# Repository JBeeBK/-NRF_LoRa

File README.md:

# NRF_LoRa

PCB design for a Nordic nRF52840 (QFN48) with SX1262 LoRa module.  
Designed as a low-power mesh node for experimentation and LoRaWan or Meshtastic development.

### Features
- nRF52840 SoC (BLE, Cortex-M4F)
- SX1262 LoRa (868 MHz) with SMA antenna
- USB-C input with TPS2116 power multiplexer
- MCP73831 LiPo charger and MAX17048 fuel gauge
- 2 x I²C headers for OLED and maybe card keyboard
- FT231XS USB-UART bridge for programming
- Compact 4-layer PCB (60 x 45 mm)
- Additional Header for 2GPIO

### Repository Structure
- `Hardware/` – KiCad source files (schematic, PCB, symbols, footprints)
- `Documents/` – Excel for pinout and pins used, net labels, etc.
- `Output_Pcb/` – Gerbers, fabrication layer PDFs
- `Output_Assembly/` – BOM, pick-and-place, schematic PDFs
- `Firmware/` – C++ file

This repo documents the hardware design; firmware will be added once the board is fabricated.

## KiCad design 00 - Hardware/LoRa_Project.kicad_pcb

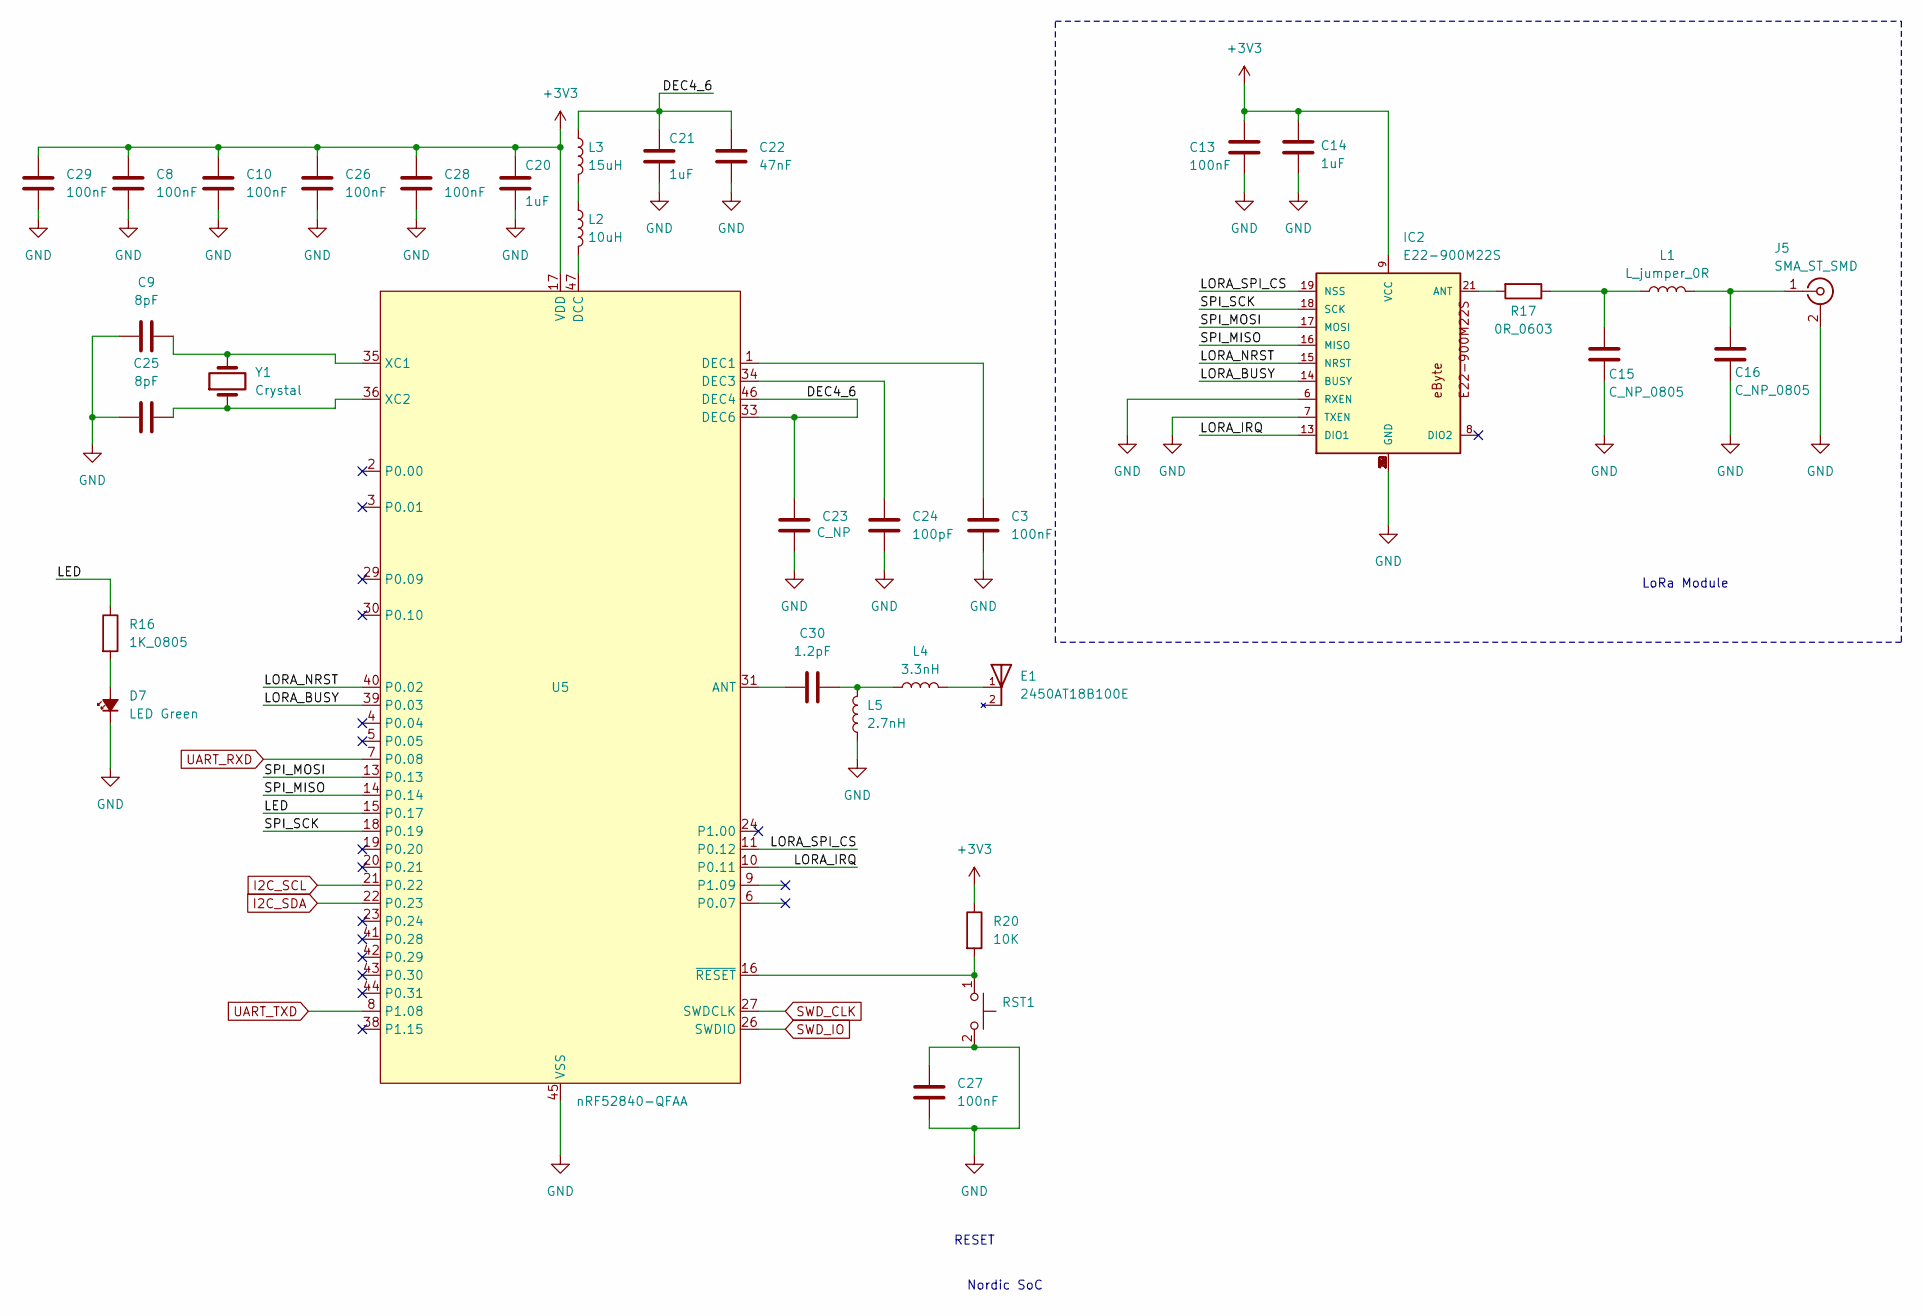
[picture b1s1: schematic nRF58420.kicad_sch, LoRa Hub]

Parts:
C3, C13, C27: 100nF; C_0603_1608Metric; MPN1 06033D104KAT2A
C8, C10, C26, C28, C29: 100nF; C_0402_1005Metric; MPN1 0402YC104KAT2A
C9, C25: 8pF; C_0603_1608Metric; MPN1 06033A8R0DAT2A
C14: 1uF; C_0805_2012Metric; MPN1 08053C105KAT2A
C15, C16: C_NP_0805; C_0805_2012Metric; MPN1 ---
C20, C21: 1uF; C_0603_1608Metric; MPN1 C0603C105K3RACTU
C22: 47nF; C_0603_1608Metric; MPN1 C0603X473J3RAC3316
C23: C_NP; C_0603_1608Metric; MPN1 ---
C24: 100pF; C_0603_1608Metric; MPN1 06033C101JAT4A
C30: 1.2pF; C_0402_1005Metric; MPN1 500R07S1R2BV4T
D7: LED Green; LED_0805; MPN1 APTD2012LCGCK
E1: 2450AT18B100E; XDCR_2450AT18B100E; MPN1 2450AT18B100E
IC2: E22-900M22S; MPN1 E22-900M22S
J5: SMA_ST_SMD; MPN1 CONSMA001-SMD-G
L1: L_jumper_0R; L_0805_2012Metric; MPN1 CRCW08050000Z0EA
L2: 10uH; L_0603_1608Metric; MPN1 LQW18AS10NG0ZD
L3: 15uH; L_0603_1608Metric; MPN1 LQW18AS10NG0ZD
L4: 3.3nH; L_0402_1005Metric; MPN1 L-07C3N3SV6T
L5: 2.7nH; L_0402_1005Metric; MPN1 L-07C2N7SV6T
R16: 1K_0805; R_0805_2012Metric; MPN1 CRCW08051K00FKEA
R17: 0R_0603; R_0603_1608Metric; MPN1 CRCW06030000Z0EAC
R20: 10K; R_0805_2012Metric; MPN1 CRCW080510K0FKEA
RST1: SW_Push_1P1T_NO_CK_KMR2; MPN1 KMR211NGLFS
U5: nRF52840-QFAA; QFN-48-1EP_6x6mm_P0.4mm_EP4.6x4.6mm_ThermalVias; MPN1 nRF52840-QFN
Y1: Crystal; Crystal_SMD_2016-4Pin_2.0x1.6mm; MPN1 XRCGB32M000F1SBJR0

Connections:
/nRF52840 and LoRa/DEC4_6: C21.1, C22.1, C23.1, L3.1, U5.33 (DEC6), U5.46 (DEC4)
/nRF52840 and LoRa/LED: R16.1, U5.15 (P0.17)
/nRF52840 and LoRa/LORA_BUSY: IC2.14 (BUSY), U5.39 (P0.03)
/nRF52840 and LoRa/LORA_IRQ: IC2.13 (DIO1), U5.10 (P0.11)
/nRF52840 and LoRa/LORA_NRST: IC2.15 (NRST), U5.40 (P0.02)
/nRF52840 and LoRa/LORA_SPI_CS: IC2.19 (NSS), U5.11 (P0.12)
/nRF52840 and LoRa/SPI_MISO: IC2.16 (MISO), U5.14 (P0.14)
/nRF52840 and LoRa/SPI_MOSI: IC2.17 (MOSI), U5.13 (P0.13)
/nRF52840 and LoRa/SPI_SCK: IC2.18 (SCK), U5.18 (P0.19)
GND: C3.2, C8.2, C9.1, C10.2, C13.2, C14.2, C15.2, C16.2, C20.2, C21.2, C22.2, C23.2, C24.2, C25.1, C26.2, C27.1, C27.2, C28.2, C29.2, D7.1 (K), IC2.1 (GND), IC2.2 (GND), IC2.3 (GND), IC2.4 (GND), IC2.5 (GND), IC2.6 (RXEN), IC2.7 (TXEN), IC2.10 (GND), IC2.11 (GND), IC2.12 (GND), IC2.20 (GND), IC2.22 (GND), J5.2 (Ext), L5.1, RST1.2, RST1.3, U5.32 (VSS_PA), U5.45 (VSS), U5.49 (VSS); also elsewhere on the board
I2C_SCL: U5.21 (P0.22); also elsewhere on the board
I2C_SDA: U5.22 (P0.23); also elsewhere on the board
unnamed: C15.1, L1.1, R17.1
unnamed: C30.2, L4.1, L5.2
unnamed: D7.2 (A), R16.2
unnamed: E1.1, L4.2
unnamed: IC2.21 (ANT), R17.2
unnamed: C16.1, J5.1 (In), L1.2
unnamed: L2.1, L3.2
unnamed: C30.1, U5.31 (ANT)
unnamed: L2.2, U5.47 (DCC)
unnamed: C3.1, U5.1 (DEC1)
unnamed: C24.1, U5.34 (DEC3)
unnamed: C9.2, U5.35 (XC1), Y1.2, Y1.3
unnamed: C25.2, U5.36 (XC2), Y1.1
unnamed: R20.2, RST1.1, RST1.4, U5.16 (~RESET)
SWD_CLK: U5.27 (SWDCLK); also elsewhere on the board
SWD_IO: U5.26 (SWDIO); also elsewhere on the board
UART_RXD: U5.7 (P0.08); also elsewhere on the board
UART_TXD: U5.8 (P1.08); also elsewhere on the board

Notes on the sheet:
LoRa Module
Nordic SoC
RESET

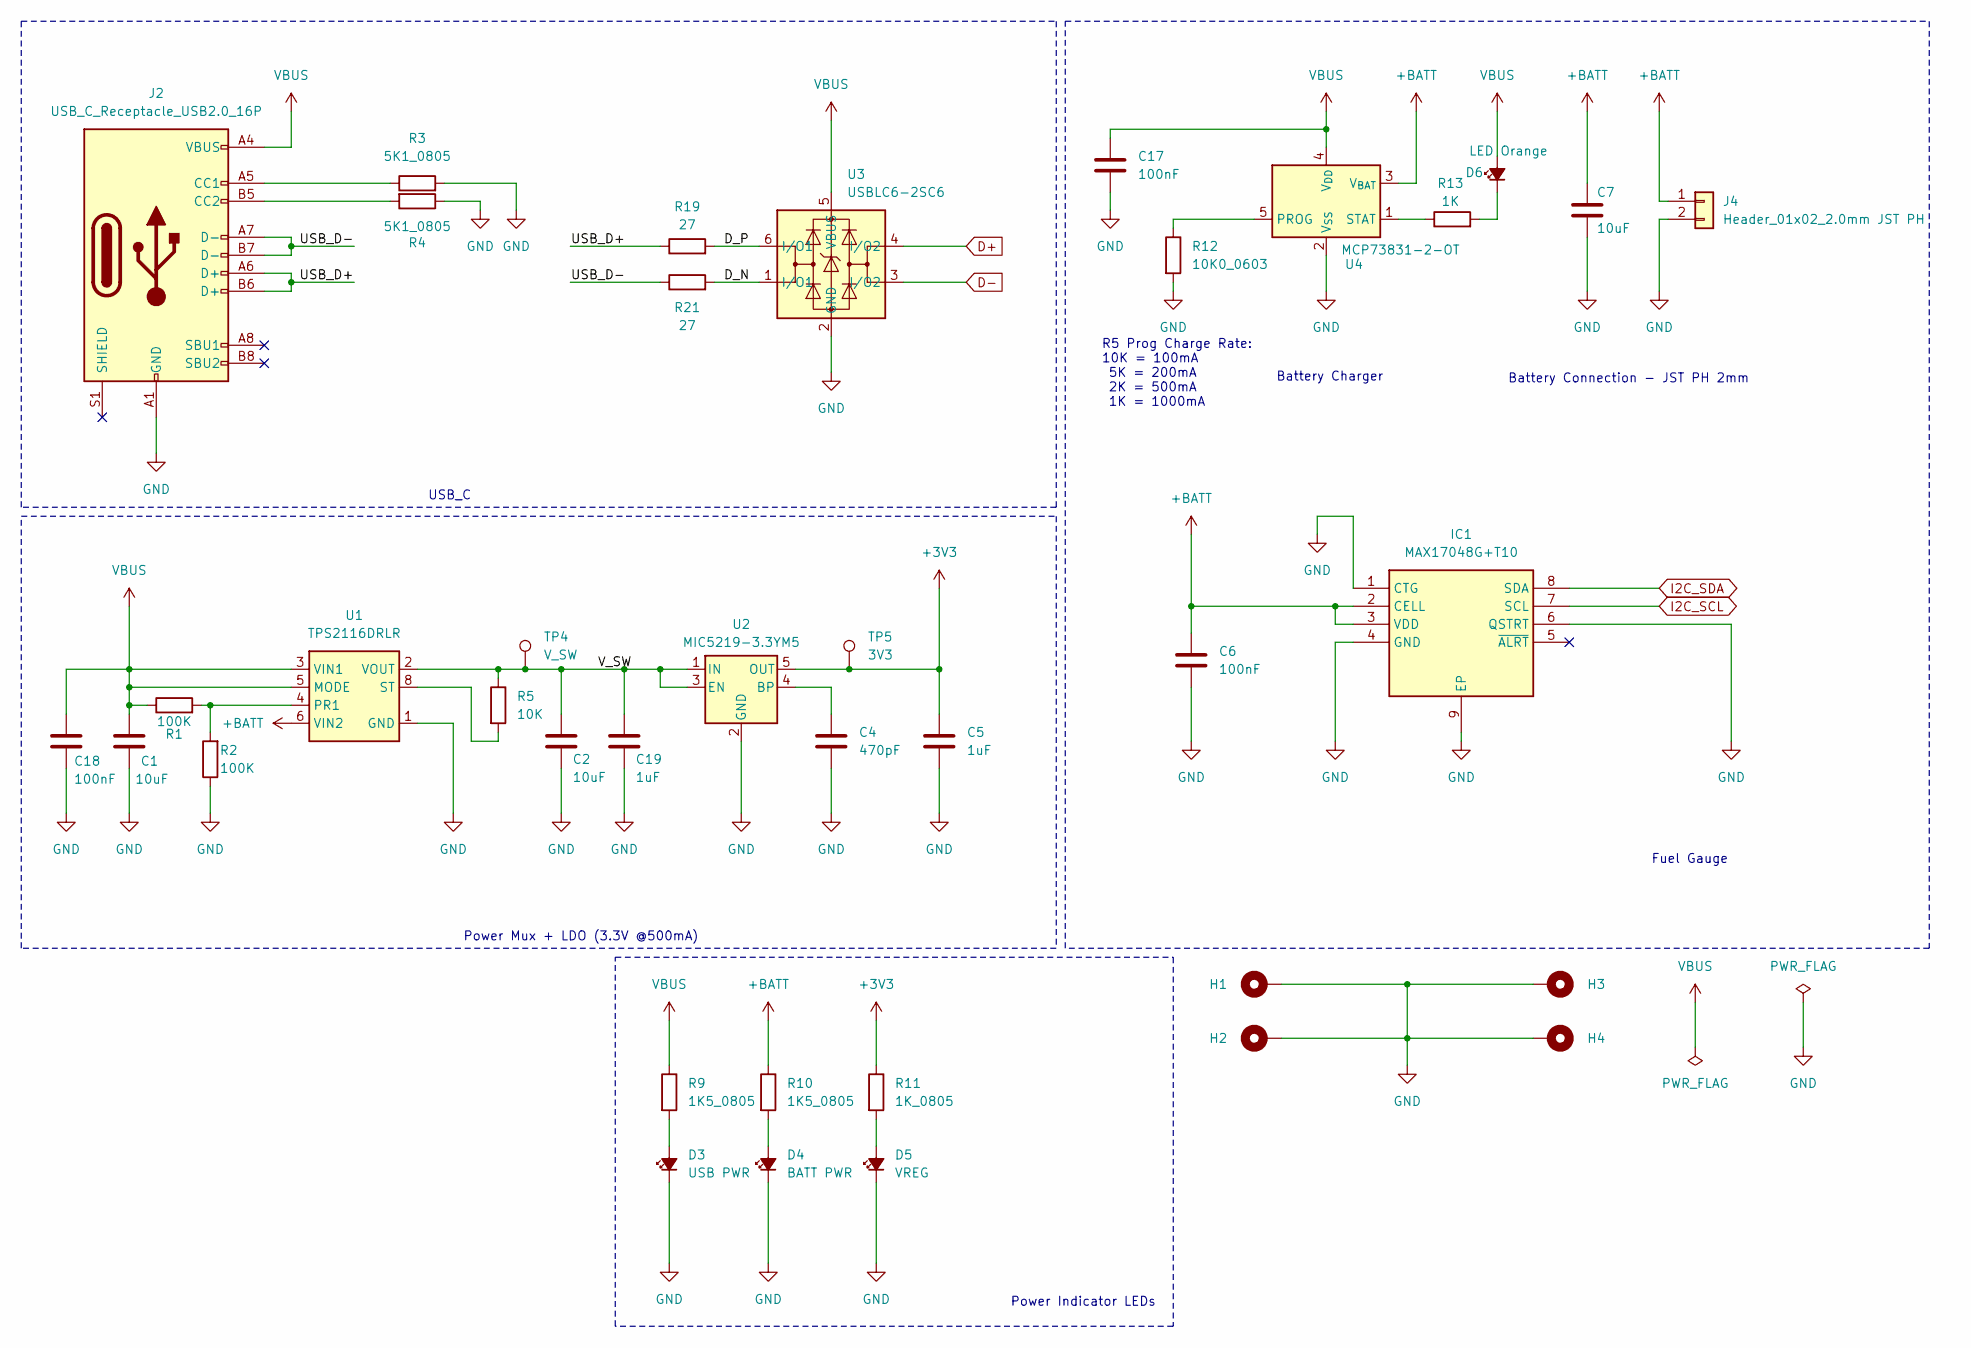
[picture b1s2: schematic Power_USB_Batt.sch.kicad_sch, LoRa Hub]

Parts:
C1, C2: 10uF; C_0603_1608Metric; MPN1 0603ZD106MAT4A
C4: 470pF; C_0805_2012Metric; MPN1 08051A471KAT2A
C5, C19: 1uF; C_0805_2012Metric; MPN1 08053C105KAT2A
C6, C17, C18: 100nF; C_0805_2012Metric; MPN1 08051C104KAT2A
C7: 10uF; C_1210_3225Metric; MPN1 C3225X7R1H106K250AC
D3: USB PWR; LED_0805; MPN1 APTD2012LSURCK
D4: BATT PWR; LED_0805; MPN1 APTD2012LSURCK
D5: VREG; LED_0805; MPN1 APTD2012LSURCK
D6: LED Orange; LED_0805; MPN1 APTD2012LCGCK
H1, H2, H3, H4: MountingHole_Pad_M3; MountingHole_3.2mm_M3_DIN965_Pad_TopBottom
IC1: MAX17048G+T10; SON50P200X200X80-9N-D; Mouser Part Number 700-MAX17048G+T10
J2: USB_C_Receptacle_USB2.0_16P; USB_C_Receptacle_GCT_USB4110; MPN1 USB4110-GF-A
J4: Header_01x02_2.0mm JST PH; JST_S2B-PH-SM4-TB_LF__SN_; MPN1 S2B-PH-SM4-TB
R1, R2: 100K; R_0603_1608Metric; MPN1 ERJ-3EKF1003V
R3, R4: 5K1_0805; R_0805_2012Metric; MPN1 CRCW08055K10FKEA
R5: 10K; R_0805_2012Metric; MPN1 CRCW080510K0FKEA
R9, R10: 1K5_0805; R_0805_2012Metric; MPN1 CRCW08051K50FKEA
R11: 1K_0805; R_0805_2012Metric; MPN1 CRCW08051K00FKEA
R12: 10K0_0603; R_0603_1608Metric; MPN1 ERJ-3EKF1002V
R13: 1K; R_0603_1608Metric; MPN1 ERJ-PA3F1001V
R19, R21: 27; R_0603_1608Metric
TP4: V_SW; TestPoint_Pad_D1.0mm; MPN1 ---
TP5: 3V3; TestPoint_Pad_D1.0mm; MPN1 ---
U1: TPS2116DRLR; SOT-583-8; MPN1 TPS2116DRLR
U2: MIC5219-3.3YM5; SOT-23-5; MPN1 MIC5219-3.3YM5-TR
U3: USBLC6-2SC6; SOT-23-6; MPN1 USBLC6-2SC6
U4: MCP73831-2-OT; SOT-23-5; MPN1 MCP73831-2-OT

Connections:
+BATT: C6.1, C7.1, IC1.2 (CELL), IC1.3 (VDD), J4.1, R10.1, U1.6 (VIN2), U4.3 (V_{BAT})
/Power/USB_D+: J2.A6 (D+), J2.B6 (D+), R19.1
/Power/USB_D-: J2.A7 (D-), J2.B7 (D-), R21.1
/Power/V_SW: C2.1, C19.1, R5.1, TP4.1, U1.2 (VOUT), U1.7 (VOUT), U2.1 (IN), U2.3 (EN)
D+: U3.4 (I/O2); also elsewhere on the board
D-: U3.3 (I/O2); also elsewhere on the board
GND: C1.2, C2.2, C4.2, C5.2, C6.2, C7.2, C17.2, C18.2, C19.2, D3.1 (K), D4.1 (K), D5.1 (K), H1.1, H2.1, H3.1, H4.1, IC1.1 (CTG), IC1.4 (GND), IC1.6 (QSTRT), IC1.9 (EP), J2.A1 (GND), J2.A12 (GND), J2.B1 (GND), J2.B12 (GND), J4.2, R2.1, R3.2, R4.1, R12.2, U1.1 (GND), U2.2 (GND), U3.2 (GND), U4.2 (V_{SS}); also elsewhere on the board
I2C_SCL: IC1.7 (SCL); also elsewhere on the board
I2C_SDA: IC1.8 (SDA); also elsewhere on the board
unnamed: D3.2 (A), R9.2
unnamed: D4.2 (A), R10.2
unnamed: D5.2 (A), R11.2
unnamed: D6.1 (K), R13.2
unnamed: J2.A5 (CC1), R3.1
unnamed: J2.B5 (CC2), R4.2
unnamed: R19.2, U3.6 (I/O1)
unnamed: R21.2, U3.1 (I/O1)
unnamed: R1.2, R2.2, U1.4 (PR1)
unnamed: R5.2, U1.8 (ST)
unnamed: C4.1, U2.4 (BP)
unnamed: R12.1, U4.5 (PROG)
unnamed: R13.1, U4.1 (STAT)

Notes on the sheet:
Battery Connection - JST PH 2mm
R5 Prog Charge Rate: 10K = 100mA 5K = 200mA 2K = 500mA 1K = 1000mA
Battery Charger
Power Indicator LEDs
Power Mux + LDO (3.3V @500mA)
USB_C
Fuel Gauge

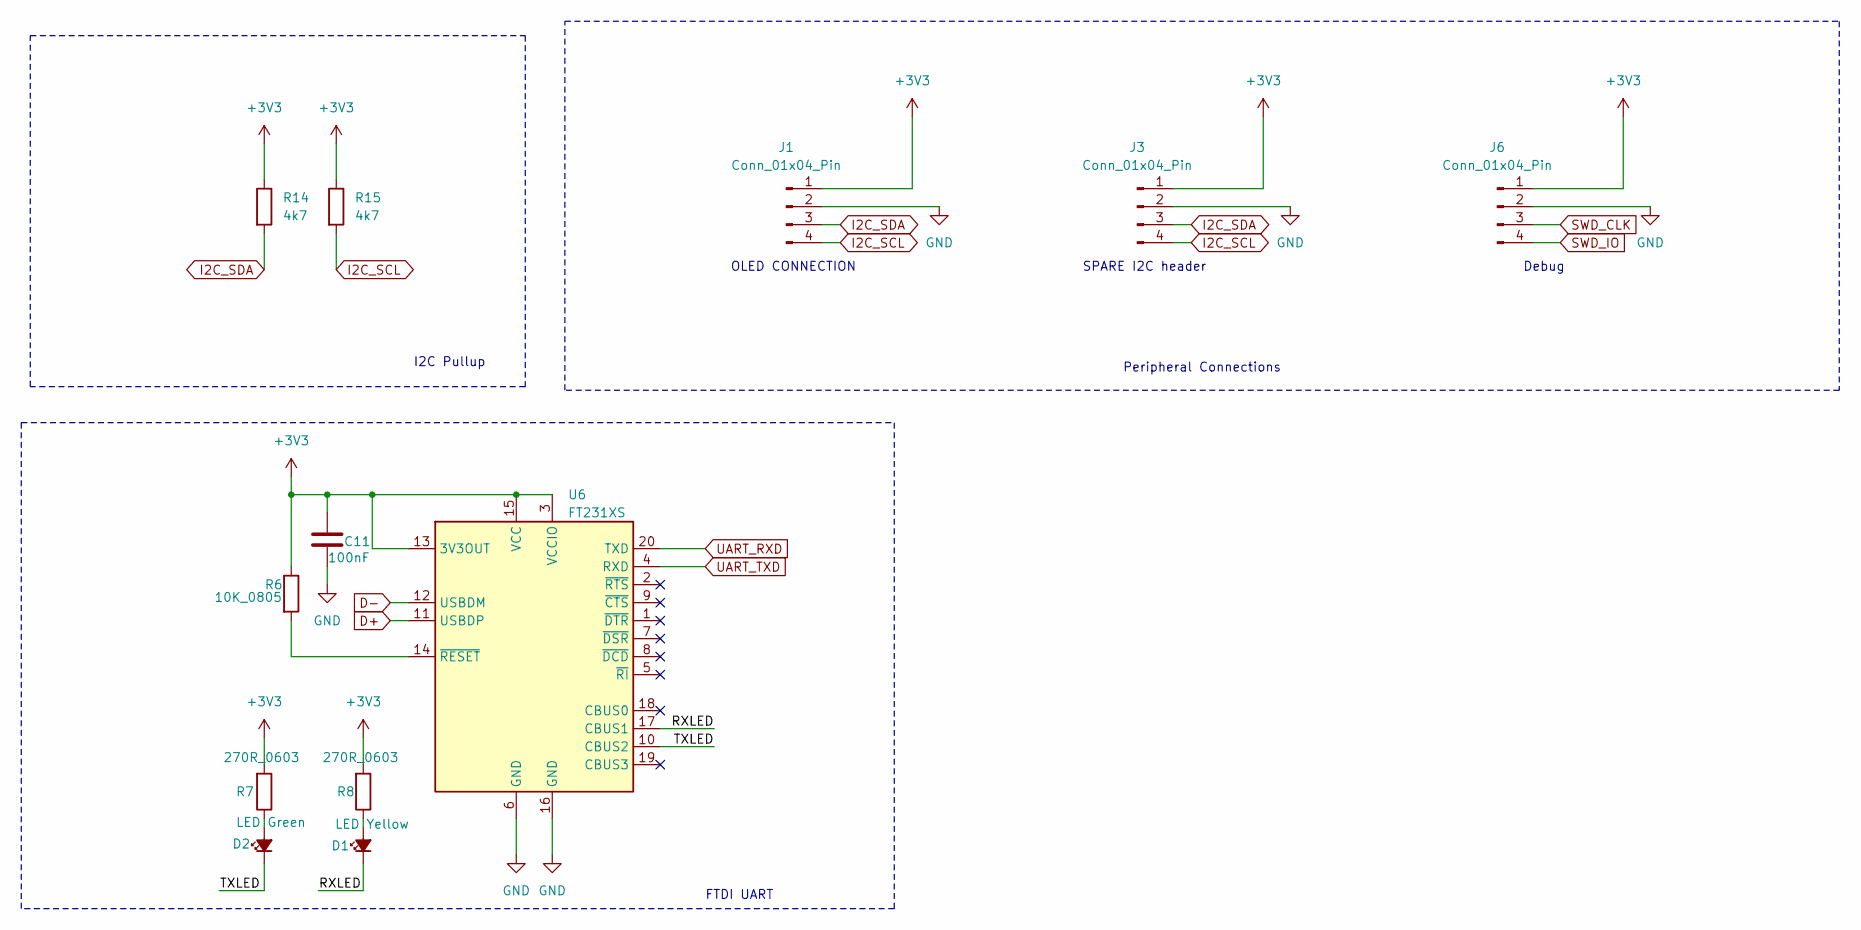
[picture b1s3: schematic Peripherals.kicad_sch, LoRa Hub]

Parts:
C11: 100nF; C_0603_1608Metric; MPN1 06033D104KAT2A
D1: LED Yellow; LED_0805; MPN1 APTD2012LCGCK
D2: LED Green; LED_0805; MPN1 APTD2012LCGCK
J1, J3, J6: Conn_01x04_Pin; PinHeader_1x04_P2.54mm_Vertical
R6: 10K_0805; R_0805_2012Metric; MPN1 CRCW080510K0FKEA
R7, R8: 270R_0603; R_0603_1608Metric; MPN1 ERJ-UP3F2700V
R14, R15: 4k7; R_0402_1005Metric_Pad0.72x0.64mm_HandSolder; MPN1 560112110245
U6: FT231XS; SSOP-20_3.9x8.7mm_P0.635mm; MPN1 FT231XS

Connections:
/Peripherals/RXLED: D1.1 (K), U6.17 (CBUS1)
/Peripherals/TXLED: D2.1 (K), U6.10 (CBUS2)
D+: U6.11 (USBDP); also elsewhere on the board
D-: U6.12 (USBDM); also elsewhere on the board
GND: C11.1, J1.2, J3.2, J6.2, U6.6 (GND), U6.16 (GND); also elsewhere on the board
I2C_SCL: J1.4, J3.4, R15.2; also elsewhere on the board
I2C_SDA: J1.3, J3.3, R14.2; also elsewhere on the board
unnamed: D1.2 (A), R8.2
unnamed: D2.2 (A), R7.2
SWD_CLK: J6.3; also elsewhere on the board
SWD_IO: J6.4; also elsewhere on the board
UART_RXD: U6.20 (TXD); also elsewhere on the board
UART_TXD: U6.4 (RXD); also elsewhere on the board

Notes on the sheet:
Debug
FTDI UART
I2C Pullup
OLED CONNECTION
Peripheral Connections
SPARE I2C header

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
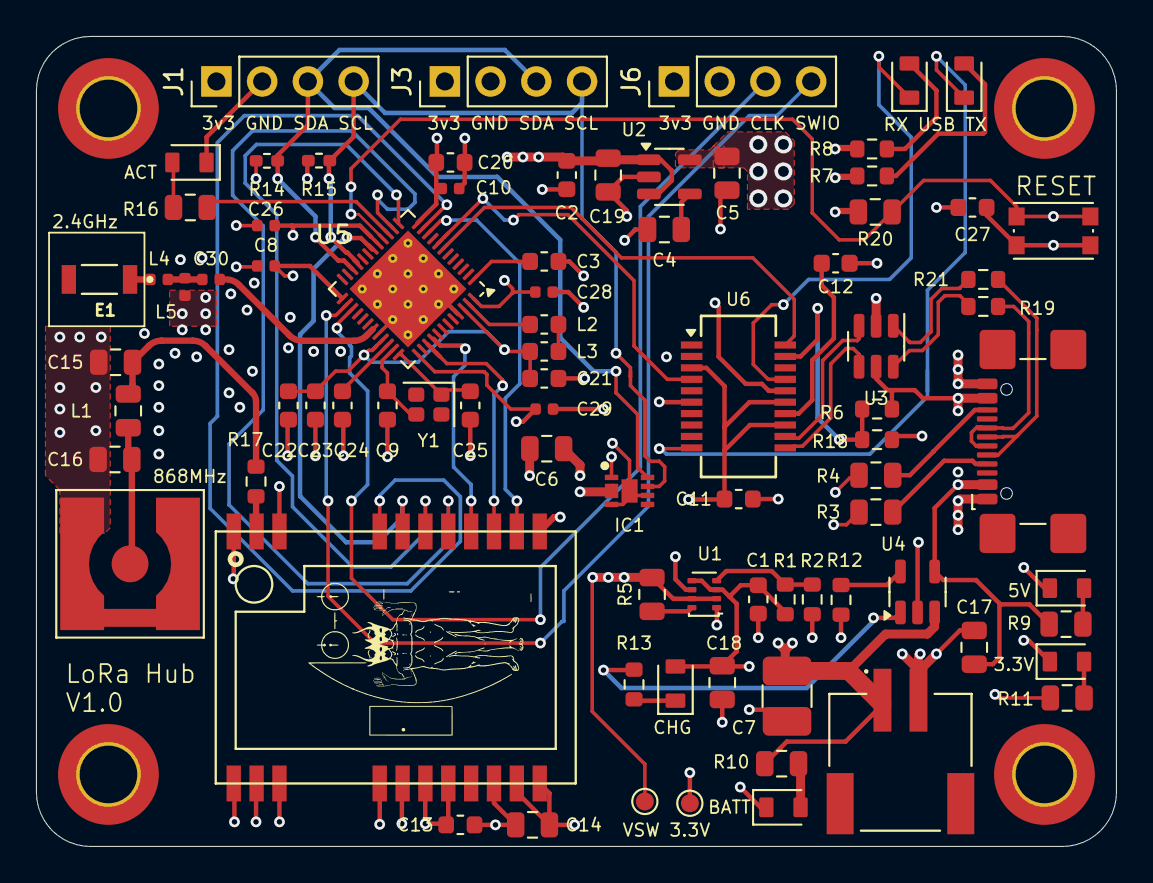
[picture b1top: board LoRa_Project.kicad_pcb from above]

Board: 4 copper layers, 60.0 x 45.0 mm, 86 parts (0 on the bottom side), 57 nets.

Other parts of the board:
C12: 100nF; C_0603_1608Metric
R18: 10K; R_0603_1608Metric

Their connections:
GND: C12.2, R18.2; also elsewhere on the board

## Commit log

2025-07-18 Added PDF Schematic to output assy
2025-07-18 updated FDTI cbus connections
2025-07-18 Rename folders to remove spaces for clean linking
2025-07-18 Updated file structure
2025-07-21 Removed SMA for GPIO header placement.
2025-07-21 updated some library files/3d
2025-07-23 Antenna output changed to fully isolate path
2025-07-24 updated silkscreen
2025-07-27 updated from generated script
2025-09-12 Missing cap 3d info. how embarassing.
2025-10-30 Added V1.0 assembly and testing notes, removed traces from ESD to move it V1.1
